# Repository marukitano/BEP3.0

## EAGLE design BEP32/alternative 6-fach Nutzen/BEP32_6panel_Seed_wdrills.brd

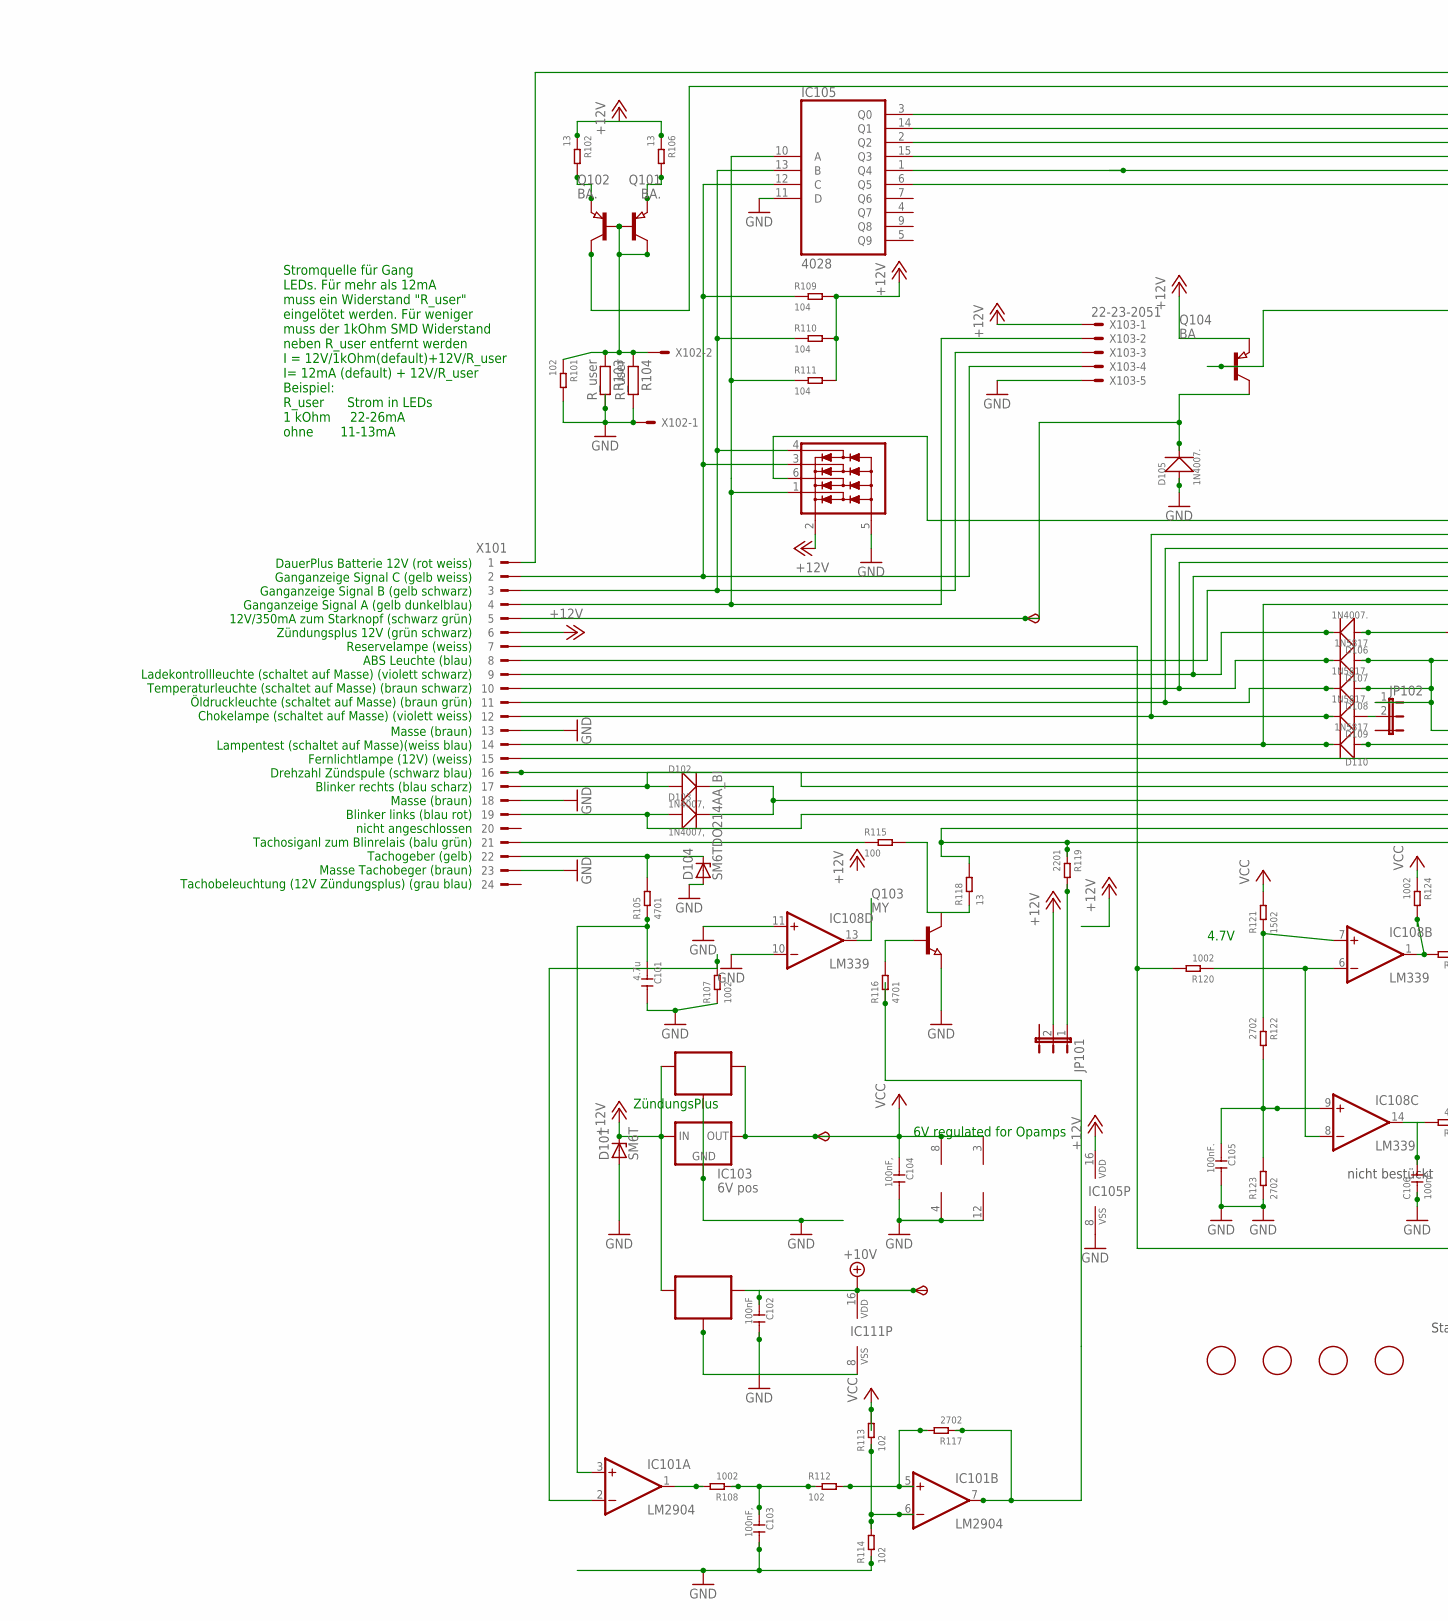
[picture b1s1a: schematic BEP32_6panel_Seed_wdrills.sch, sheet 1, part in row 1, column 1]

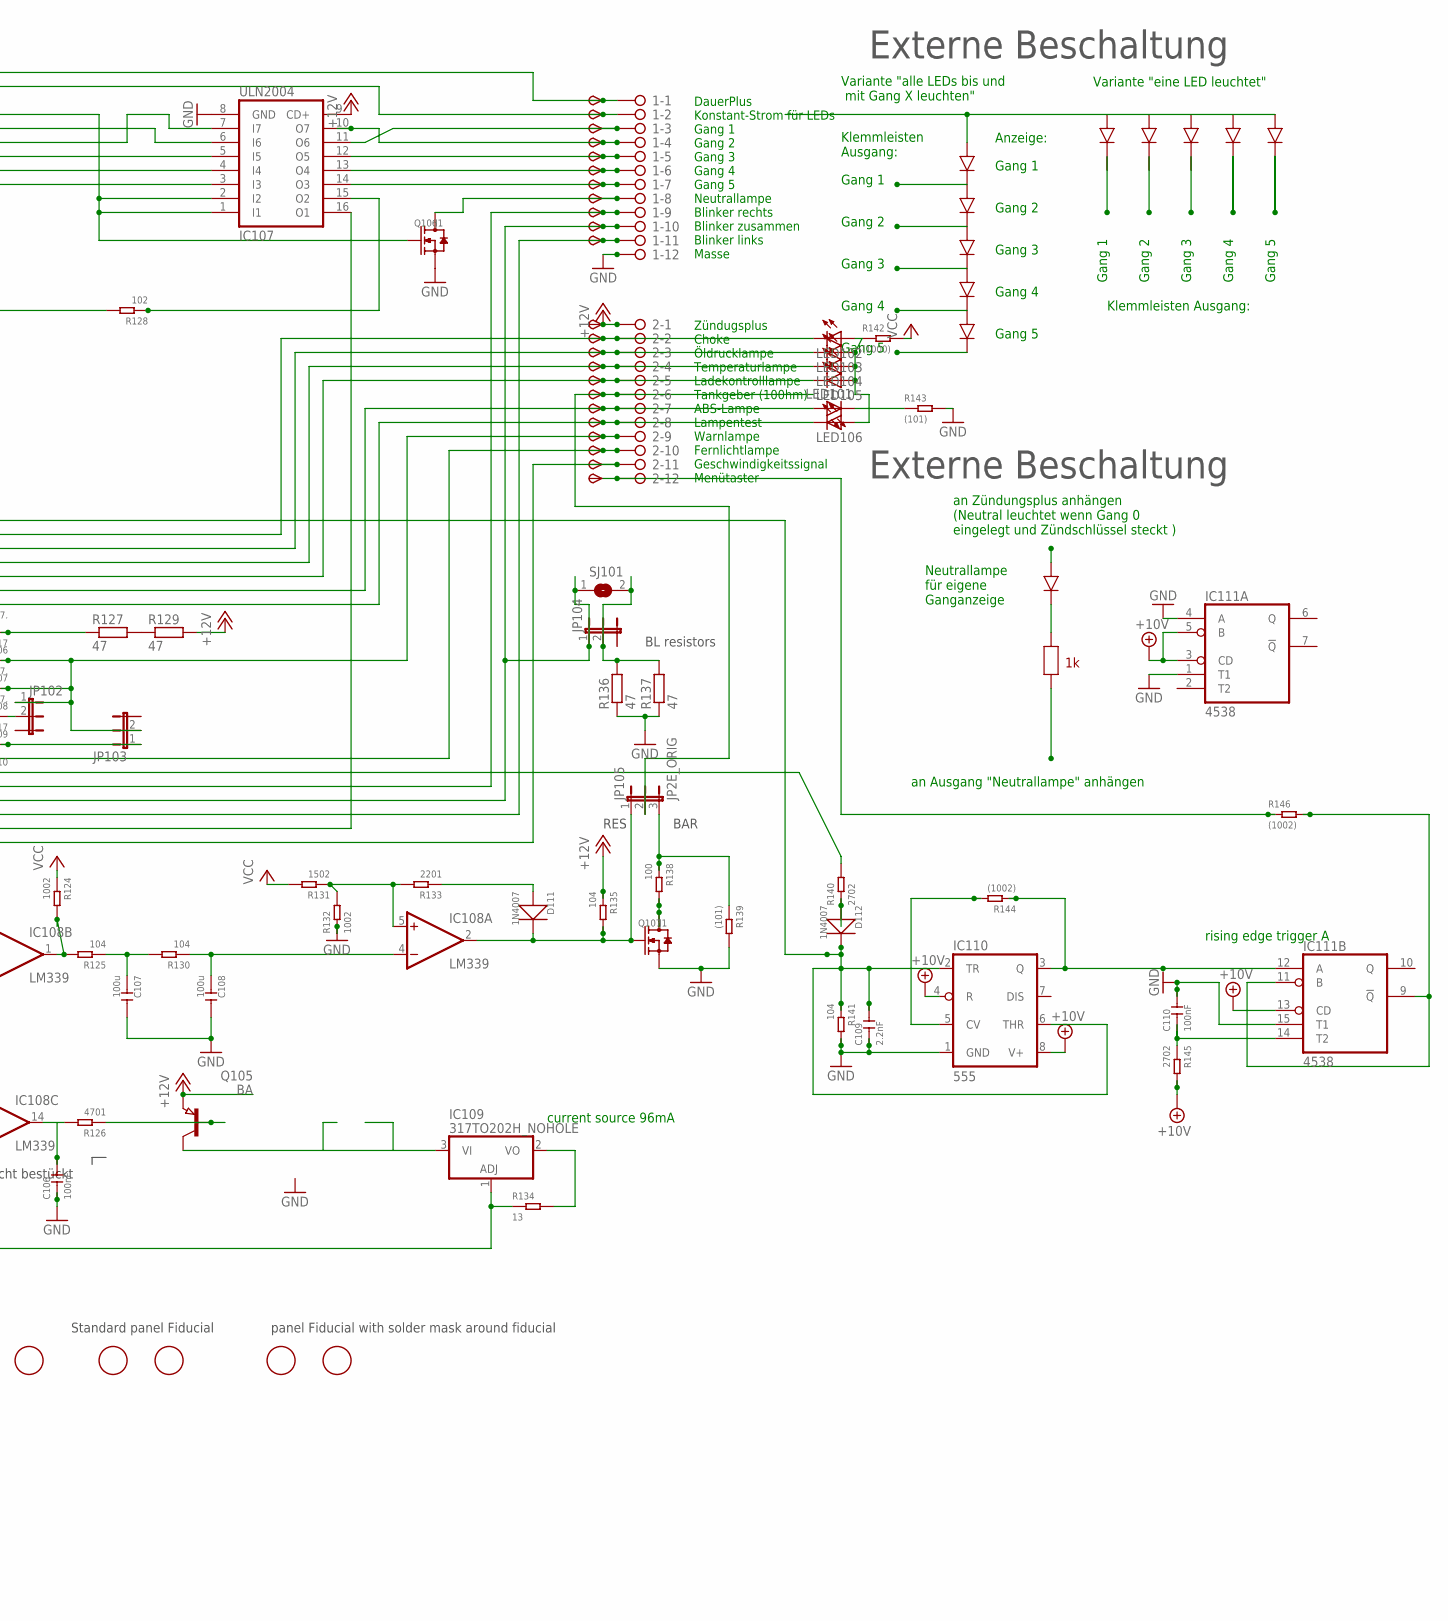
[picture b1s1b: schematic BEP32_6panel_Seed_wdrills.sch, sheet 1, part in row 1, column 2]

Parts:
1, 2: 2081-1132; 12-PIN
6V, 10V: TPSB2.0; B2.0
C101: 4.7u; C0805
C102, C110: 100nF; C0805
C103, C104: 100nF,; C0805
C105, C106: 100nF.; C0805
C107, C108: 100u; C1206
C109: 2.2nF; C0805
D101: SM6T; DO214AA
D102, D103: 1N4007,; DO-214AC
D104: SM6TDO214AA_BI; DO214AA_BI
D105, D106: 1N4007.; DO-214AC
D107, D110: 1N5817; DO-214AC_SLIM
D108, D109: 1N5817.; DO-214AC_SLIM
D111, D112: 1N4007; DO-214AC
FID1, FID2, FID101, FID102, FID103, FID104: FIDUCIAL; FIDUCIAL_1MM
FID1B, FID2B: FIDUCIALFIDUCIAL_1MM_WITH_SOLDERMASK; FIDUCIAL_1MM_WITH_SOLDERMASK
IC101: LM2904; SO08
IC102: 78L06; SOT89_ROUND
IC103: 6V pos; 78LXX
IC104: 78L10; SOT89_ROUND
IC105: 4028; SO16
IC106: NUP4304SOT457_R; SOT457R_PHILIPS
IC107: ULN2004; SO16
IC108: LM339; SO14
IC109: 317TO202H_NOHOLE; TO220H_NOHOLE
IC110: 555; SO08
IC111: 4538; SO16
JP101, JP102, JP103, JP104: JP2EJP2_SMALLPADS; JP2_SMALLPADS
JP105: JP2E_ORIG; JP2_ORIG_SMALLPADS
LED101, LED102, LED103, LED104, LED105, LED106: LEDLD260; LD260
Q101, Q102: BA.; SOT89
Q103: MY; SOT89
Q104, Q105: BA; SOT89
Q106, Q107: J1; SOT-23
R101, R112, R113, R114, R128: 102; R0805
R102, R106, R118, R134: 13; R1206
R103, R104: R_user; R0805
R105, R116, R126: 4701; R0805
R107, R108, R120, R124, R132: 1002; R0805
R109, R110, R111, R125, R130, R135, R141: 104; R0805
R115, R138: 100; R0805
R117, R122, R123, R140, R145: 2702; R0805
R119, R133: 2201; R0805
R121, R131: 1502; R0805
R127, R129, R136, R137: 47; V235/17_1MM
R139, R143: (101); R0805
R142: (1000); R0805
R144, R146: (1002); R0805
SJ101: SJ
START: TPSB2.0; B2.0
TP1, TP2, TP3, TP4, TP5, TP6, TP7, TP8, TP9, TP10, TP11, TP12, TP13, TP16, TP17, TP18, TP19, TP21, TP22, TP23, TP25, TP26: TPSB2.0; B2.0
TP24: TPSB1,27; B1,27
X101: CON_BMWV2; 24-PIN_V2
X102: 22-23-2021
X103: 22-23-2051

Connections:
+10V: 10V.TP, C102.1, IC104.1 (OUT), IC110.4 (R), IC110.8 (V+), IC111.3 (CD), IC111.5 (B), IC111.13 (CD), IC111.16 (VDD), R145.2; also elsewhere on the board
+12V: 2.1, D101.C, IC102.3 (IN), IC103.IN, IC104.3 (IN), IC105.16 (VDD), IC106.2 (V+), IC107.9 (CD+), JP101.2, Q104.3 (E), Q105.3 (E), R102.1, R106.1, R109.2, R110.2, R111.2, R129.2, R135.1, TP12.TP, X101.6, X103.1; also elsewhere on the board
+12V1: IC101.7 (OUT), R116.1, R117.1
GND: 1.12, C101.2, C102.2, C103.2, C104.2, C105.2, C106.1, C107.2, C108.2, C109.1, C110.2, D101.A, D104.A, D105.1 (+), IC101.4 (V-), IC102.2 (GND), IC102.2@1 (GND), IC103.GND, IC104.2 (GND), IC104.2@1 (GND), IC105.8 (VSS), IC105.11 (D), IC106.5 (V-), IC107.8 (GND), IC108.10 (-IN), IC108.11 (+IN), IC108.12 (GND), IC110.1 (GND), IC111.1 (T1), IC111.4 (A), IC111.8 (VSS), IC111.15 (T1), Q103.3 (E), Q106.2 (S), Q107.2 (S), R101.2, R103.2, R104.2, R107.1, R114.1, R123.1, R132.1, R136.1, R137.1, R139.2, R141.2, R143.2, X101.13, X101.18, X101.23, X102.1, X103.5; also elsewhere on the board
unnamed: 2.9, D107.1 (+), D108.1 (+), JP102.1, JP103.2, TP24.TP
unnamed: IC105.10 (A), IC106.1 (D1), R111.1, X101.4, X103.2
unnamed: IC105.13 (B), IC106.4 (D4), R110.1, X101.3, X103.3
unnamed: 2.7, LED101.A, TP22.TP, X101.8
unnamed: Q101.3 (E), R102.2
unnamed: D111.2 (-), IC108.2 (OUT), JP105.1, Q107.1 (G), R135.2
unnamed: IC101.2 (-IN), R107.2
unnamed: R127.2, R129.1
unnamed: Q102.3 (E), R106.2
unnamed: D105.2 (-), Q104.2 (C), START.TP, X101.5
unnamed: 2.2, D109.2 (-), LED102.K (C), TP16.TP, X101.12
unnamed: 2.3, D108.2 (-), LED103.K (C), TP17.TP, X101.11
unnamed: 2.4, D107.2 (-), LED104.K (C), TP18.TP, X101.10
unnamed: IC109.3 (VI), Q105.2 (C)
unnamed: IC108.6 (-IN), IC108.8 (-IN), R120.1
unnamed: IC105.12 (C), IC106.3 (D3), R109.1, X101.2, X103.4
unnamed: IC105.15 (Q3), IC107.5 (I5)
unnamed: 2.8, D110.2 (-), LED106.K (C), TP23.TP, X101.14
unnamed: 1.9, D102.1 (+), TP9.TP, X101.17
unnamed: 1.11, D103.1 (+), TP11.TP, X101.19
unnamed: IC111.9 (!Q), IC111.11 (B), R146.2
unnamed: D104.C, R105.2, X101.22
unnamed: C101.1, IC101.3 (+IN), R105.1
unnamed: 1.6, IC107.13 (O4), TP6.TP
unnamed: 1.7, IC107.14 (O3), TP7.TP
unnamed: 2.11, IC107.16 (O1), R118.2, R119.1, TP26.TP
unnamed: 2.6, JP105.2, TP21.TP
unnamed: JP101.1, R119.2
unnamed: C105.1, IC108.9 (+IN), R122.2, R123.2
unnamed: C106.2, IC108.14 (OUT), R126.2
unnamed: C109.2, D112.2 (-), IC106.6 (D2), IC110.2 (TR), IC110.6 (THR), R141.1
unnamed: LED101.K (C), R143.1
unnamed: IC109.1 (ADJ), R120.2, R134.1, X101.7
unnamed: Q105.1 (B), R126.1
unnamed: IC105.2 (Q2), IC107.7 (I7)
unnamed: 1.3, IC107.11 (O6), TP3.TP
unnamed: 1.5, IC107.12 (O5), TP5.TP
unnamed: LED102.A, LED103.A, LED104.A, LED105.A, LED106.A, R142.1
unnamed: R140.2, X101.16
unnamed: Q104.1 (B), R128.2
unnamed: IC105.3 (Q0), IC107.1 (I1), IC107.2 (I2), Q106.1 (G)
unnamed: C107.1, R125.1, R130.2
unnamed: C108.1, IC108.4 (-IN), R130.1
unnamed: IC108.5 (+IN), R131.1, R132.2, R133.2
unnamed: Q107.3 (D), R138.2
unnamed: D111.1 (+), R133.1
unnamed: IC105.1 (Q4), IC107.4 (I4)
unnamed: R115.1, X101.21
unnamed: 1.8, Q106.3 (D), TP8.TP
unnamed: 2.10, TP25.TP, X101.15
unnamed: D106.1 (+), R127.1
unnamed: 2.5, D106.2 (-), LED105.K (C), TP19.TP, X101.9
unnamed: IC105.14 (Q1), IC107.6 (I6)
unnamed: Q101.1 (B), Q102.1 (B), Q102.2 (C), R101.1, R103.1, R104.1, X102.2
unnamed: Q103.2 (C), R115.2, R118.1
unnamed: 1.2, Q101.2 (C), TP2.TP
unnamed: IC105.6 (Q5), IC107.3 (I3)
unnamed: IC109.2 (VO), R134.2
unnamed: IC110.5 (CV), R144.2
unnamed: 1.4, IC107.10 (O7), TP4.TP
unnamed: 1.1, TP1.TP, X101.1
unnamed: IC108.7 (+IN), R121.1, R122.1
unnamed: Q103.1 (B), R116.2
unnamed: IC110.3 (Q), IC111.12 (A), R144.1
unnamed: D112.1 (+), R140.1
unnamed: IC107.15 (O2), R128.1
unnamed: C110.1, IC111.14 (T2), R145.1
unnamed: 2.12, R146.1, TP13.TP
unnamed: IC101.1 (OUT), R108.2
unnamed: 1.10, D102.2 (-), D103.2 (-), JP104.1, SJ101.1, TP10.TP
unnamed: JP104.2, R136.2, R137.2, SJ101.2
unnamed: D109.1 (+), JP102.2
unnamed: C103.1, R108.1, R112.1
unnamed: IC101.5 (+IN), R112.2, R117.2
unnamed: D110.1 (+), JP103.1
unnamed: JP105.3, R138.1, R139.1
unnamed: IC101.6 (-IN), R113.1, R114.2
unnamed: IC108.1 (OUT), R124.2, R125.2
VCC: 6V.TP, C104.1, IC101.8 (V+), IC102.1 (OUT), IC103.OUT, IC108.3 (V+), R113.2, R121.2, R124.1, R131.2, R142.2; also elsewhere on the board

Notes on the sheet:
6V regulated for Opamps
current source 96mA
ZündungsPlus
Zündugsplus Choke Öldrucklampe Temperaturlampe Ladekontrolllampe Tankgeber (100hm) ABS-Lampe Lampentest Warnlampe Fernlichtlampe Geschwindigkeitssignal Menütaster
DauerPlus Konstant-Strom für LEDs Gang 1 Gang 2 Gang 3 Gang 4 Gang 5 Neutrallampe Blinker rechts Blinker zusammen Blinker links Masse
DauerPlus Batterie 12V (rot weiss) Ganganzeige Signal C (gelb weiss) Ganganzeige Signal B (gelb schwarz) Ganganzeige Signal A (gelb dunkelblau) 12V/350mA zum Starknopf (schwarz grün) Zündungsplus 12V (grün schwarz) Reservelampe (weiss) ABS Leuchte (blau) Ladekontrollleuchte (schaltet auf Masse) (vi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
Masse (braun) Lampentest (schaltet auf Masse)(weiss blau) Fernlichtlampe (12V) (weiss) Drehzahl Zündspule (schwarz blau) Blinker rechts (blau scharz) Masse (braun) Blinker links (blau rot) nicht angeschlossen Tachosiganl zum Blinrelais (balu grün) Tachogeber (gelb) Masse Tachobeger (braun) Tachobel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
4.7V
Stromquelle für Gang LEDs. Für mehr als 12mA muss ein Widerstand "R_user" eingelötet werden. Für weniger muss der 1kOhm SMD Widerstand neben R_user entfernt werden I = 12V/1kOhm(default)+12V/R_user I= 12mA (default) + 12V/R_user Beispiel: R_user Strom in LEDs 1 kOhm 22-26mA ohne 11-13mA
Gang 1
Gang 2
Gang 3
Gang 4
Gang 5
Variante "eine LED leuchtet"
Variante "alle LEDs bis und mit Gang X leuchten"
Klemmleisten Ausgang:
Klemmleisten Ausgang:
an Zündungsplus anhängen (Neutral leuchtet wenn Gang 0 eingelegt und Zündschlüssel steckt )
an Ausgang "Neutrallampe" anhängen
Neutrallampe für eigene Ganganzeige
Externe Beschaltung
Anzeige:
nicht bestückt
rising edge trigger A
BAR
RES
BL resistors
Standard panel Fiducial
panel Fiducial with solder mask around fiducial

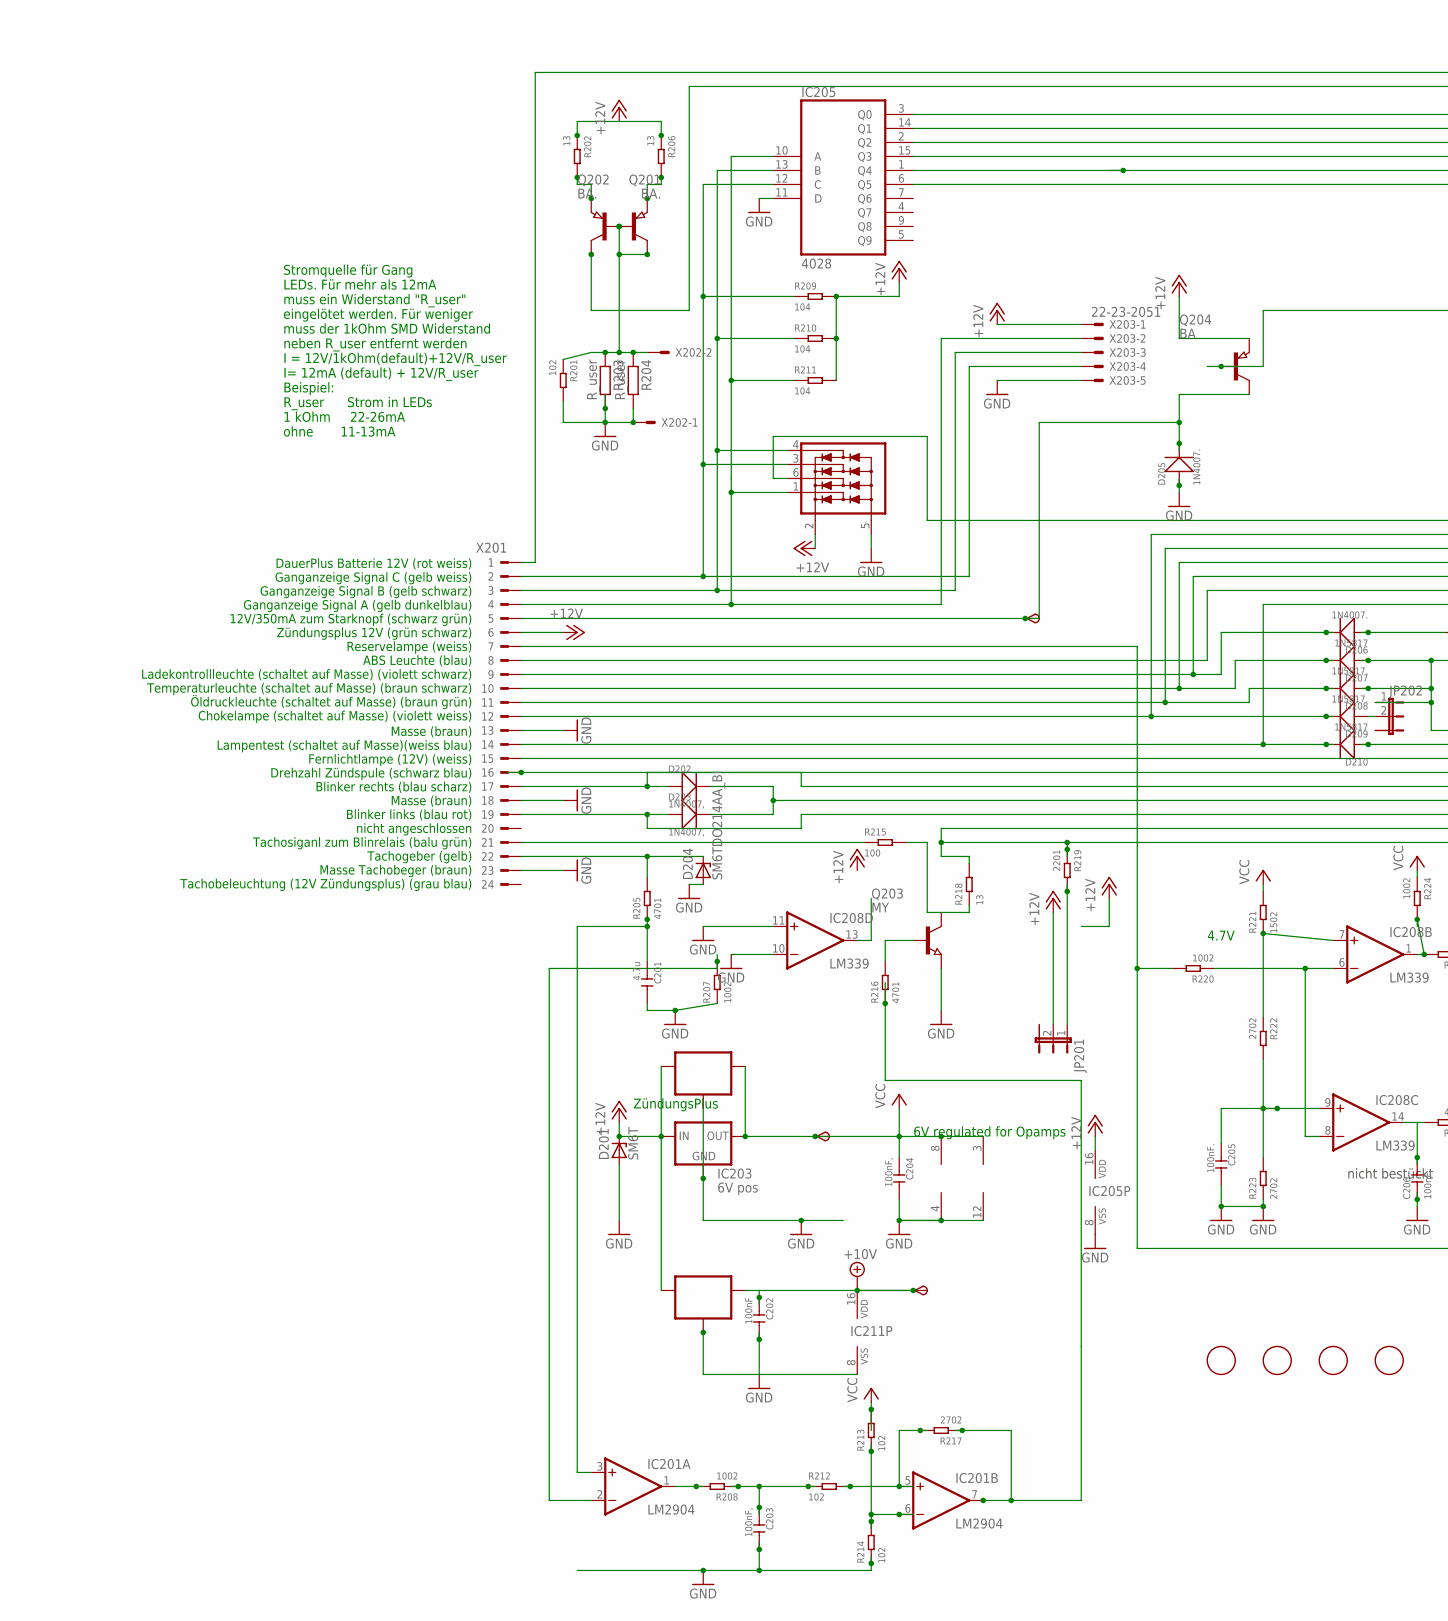
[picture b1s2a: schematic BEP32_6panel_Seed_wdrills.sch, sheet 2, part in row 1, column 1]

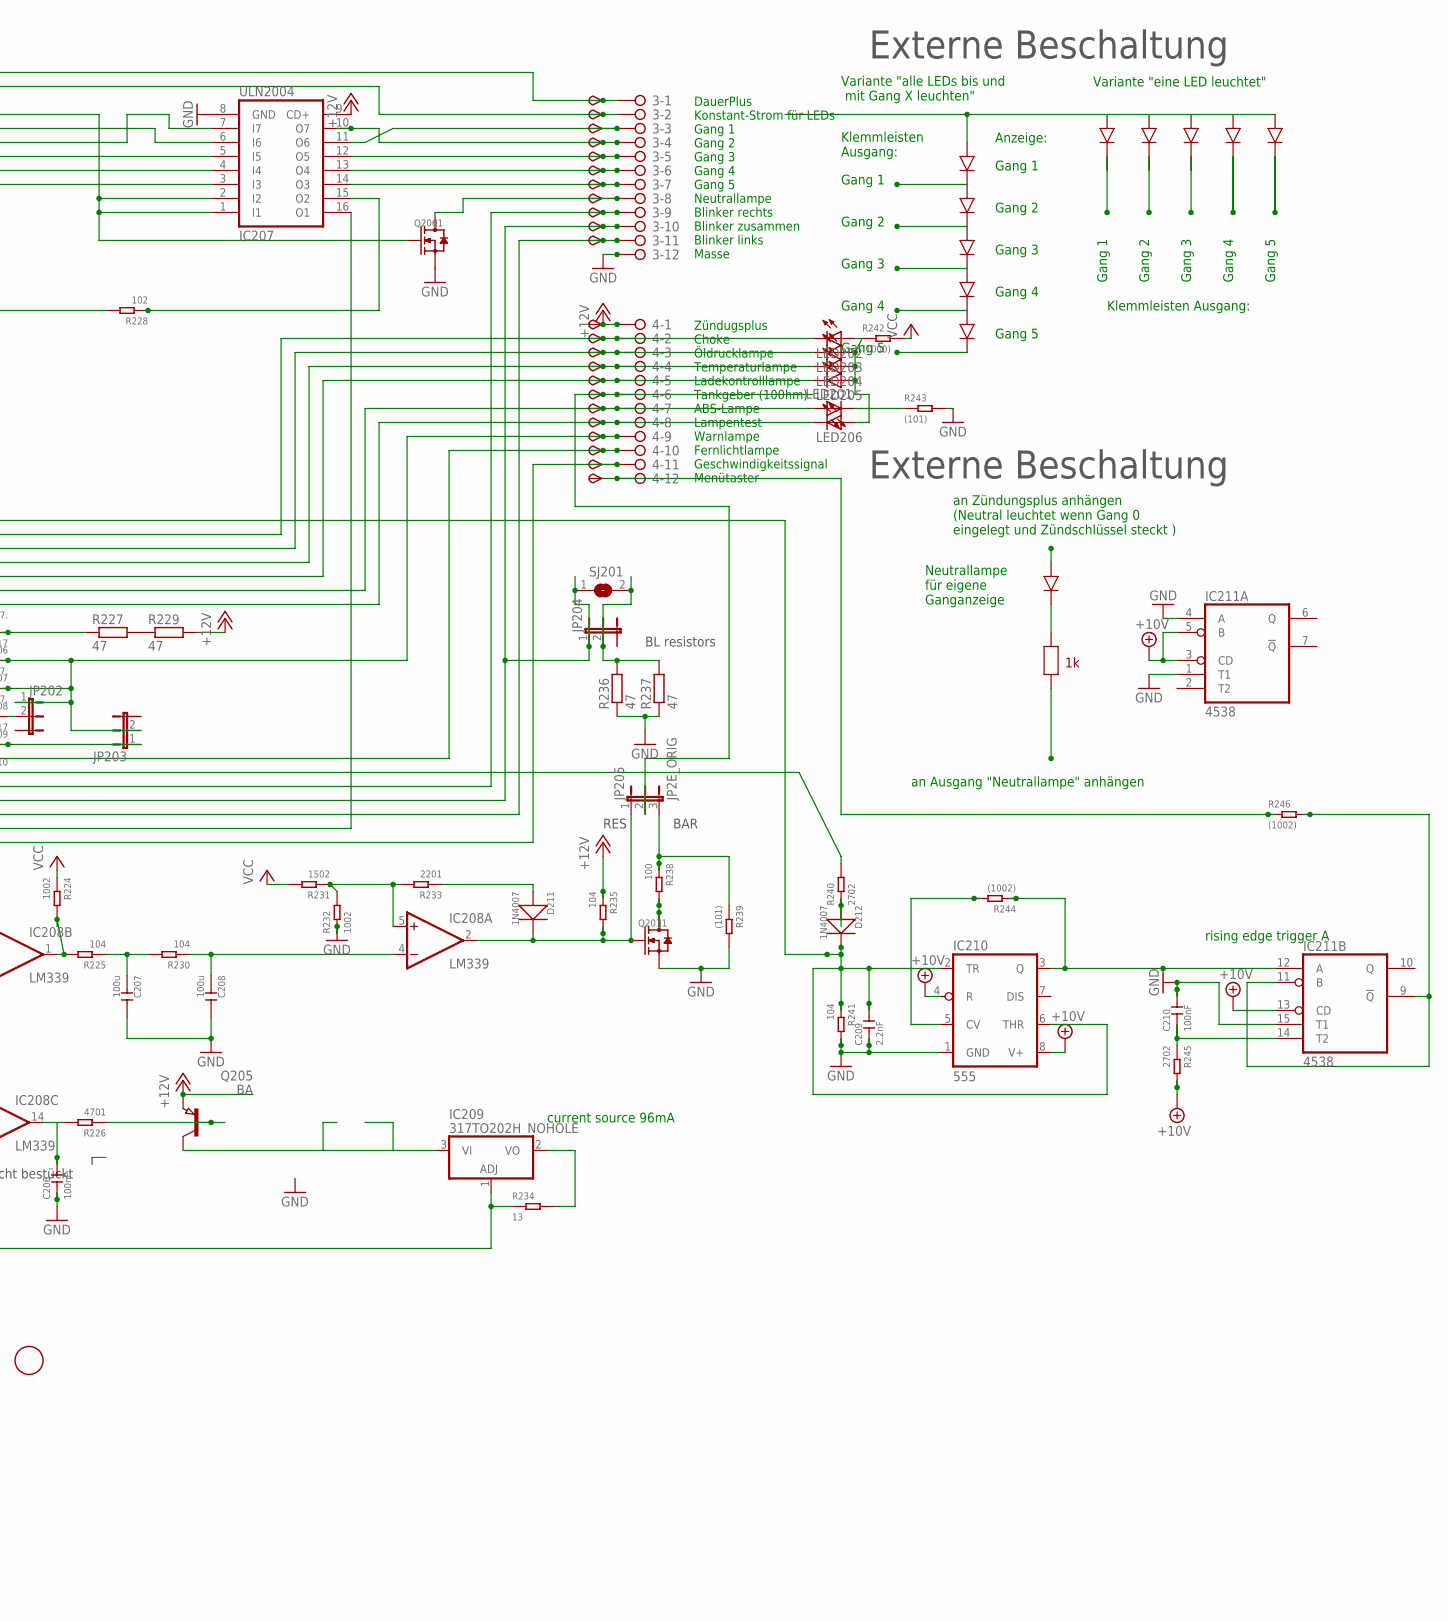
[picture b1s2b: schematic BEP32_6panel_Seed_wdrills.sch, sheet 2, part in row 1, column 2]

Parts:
3, 4: 2081-1132; 12-PIN
6V201, 10V201: TPSB2.0; B2.0
C201: 4.7u; C0805
C202, C210: 100nF; C0805
C203, C204: 100nF,; C0805
C205, C206: 100nF.; C0805
C207, C208: 100u; C1206
C209: 2.2nF; C0805
D201: SM6T; DO214AA
D202, D203: 1N4007,; DO-214AC
D204: SM6TDO214AA_BI; DO214AA_BI
D205, D206: 1N4007.; DO-214AC
D207, D210: 1N5817; DO-214AC_SLIM
D208, D209: 1N5817.; DO-214AC_SLIM
D211, D212: 1N4007; DO-214AC
FID201, FID202, FID203, FID204: FIDUCIAL; FIDUCIAL_1MM
IC201: LM2904; SO08
IC202: 78L06; SOT89_ROUND
IC203: 6V pos; 78LXX
IC204: 78L10; SOT89_ROUND
IC205: 4028; SO16
IC206: NUP4304SOT457_R; SOT457R_PHILIPS
IC207: ULN2004; SO16
IC208: LM339; SO14
IC209: 317TO202H_NOHOLE; TO220H_NOHOLE
IC210: 555; SO08
IC211: 4538; SO16
JP201, JP202, JP203, JP204: JP2EJP2_SMALLPADS; JP2_SMALLPADS
JP205: JP2E_ORIG; JP2_ORIG_SMALLPADS
LED201, LED202, LED203, LED204, LED205, LED206: LEDLD260; LD260
Q201, Q202: BA.; SOT89
Q203: MY; SOT89
Q204, Q205: BA; SOT89
Q206, Q207: J1; SOT-23
R201, R212, R213, R214, R228: 102; R0805
R202, R206, R218, R234: 13; R1206
R203, R204: R_user; R0805
R205, R216, R226: 4701; R0805
R207, R208, R220, R224, R232: 1002; R0805
R209, R210, R211, R225, R230, R235, R241: 104; R0805
R215, R238: 100; R0805
R217, R222, R223, R240, R245: 2702; R0805
R219, R233: 2201; R0805
R221, R231: 1502; R0805
R227, R229, R236, R237: 47; V235/17_1MM
R239, R243: (101); R0805
R242: (1000); R0805
R244, R246: (1002); R0805
SJ201: SJ
START201: TPSB2.0; B2.0
TP14, TP15, TP20, TP27, TP28, TP29, TP30, TP31, TP32, TP33, TP34, TP35, TP36, TP37, TP38, TP39, TP40, TP41, TP43, TP44, TP45, TP46: TPSB2.0; B2.0
TP42: TPSB1,27; B1,27
X201: CON_BMWV2; 24-PIN_V2
X202: 22-23-2021
X203: 22-23-2051

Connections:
+10V: 10V201.TP, C202.1, IC204.1 (OUT), IC210.4 (R), IC210.8 (V+), IC211.3 (CD), IC211.5 (B), IC211.13 (CD), IC211.16 (VDD), R245.2; also elsewhere on the board
+12V: 4.1, D201.C, IC202.3 (IN), IC203.IN, IC204.3 (IN), IC205.16 (VDD), IC206.2 (V+), IC207.9 (CD+), JP201.2, Q204.3 (E), Q205.3 (E), R202.1, R206.1, R209.2, R210.2, R211.2, R229.2, R235.1, TP45.TP, X201.6, X203.1; also elsewhere on the board
+12V2: IC201.7 (OUT), R216.1, R217.1
GND: 3.12, C201.2, C202.2, C203.2, C204.2, C205.2, C206.1, C207.2, C208.2, C209.1, C210.2, D201.A, D204.A, D205.1 (+), IC201.4 (V-), IC202.2 (GND), IC202.2@1 (GND), IC203.GND, IC204.2 (GND), IC204.2@1 (GND), IC205.8 (VSS), IC205.11 (D), IC206.5 (V-), IC207.8 (GND), IC208.10 (-IN), IC208.11 (+IN), IC208.12 (GND), IC210.1 (GND), IC211.1 (T1), IC211.4 (A), IC211.8 (VSS), IC211.15 (T1), Q203.3 (E), Q206.2 (S), Q207.2 (S), R201.2, R203.2, R204.2, R207.1, R214.1, R223.1, R232.1, R236.1, R237.1, R239.2, R241.2, R243.2, X201.13, X201.18, X201.23, X202.1, X203.5; also elsewhere on the board
unnamed: R227.2, R229.1
unnamed: 4.9, D207.1 (+), D208.1 (+), JP202.1, JP203.2, TP42.TP
unnamed: IC205.10 (A), IC206.1 (D1), R211.1, X201.4, X203.2
unnamed: IC205.13 (B), IC206.4 (D4), R210.1, X201.3, X203.3
unnamed: D205.2 (-), Q204.2 (C), START201.TP, X201.5
unnamed: IC205.12 (C), IC206.3 (D3), R209.1, X201.2, X203.4
unnamed: 4.7, LED201.A, TP40.TP, X201.8
unnamed: 4.2, D209.2 (-), LED202.K (C), TP35.TP, X201.12
unnamed: 4.3, D208.2 (-), LED203.K (C), TP36.TP, X201.11
unnamed: 4.4, D207.2 (-), LED204.K (C), TP37.TP, X201.10
unnamed: 4.8, D210.2 (-), LED206.K (C), TP41.TP, X201.14
unnamed: 3.9, D202.1 (+), TP32.TP, X201.17
unnamed: 3.11, D203.1 (+), TP34.TP, X201.19
unnamed: D204.C, R205.2, X201.22
unnamed: C201.1, IC201.3 (+IN), R205.1
unnamed: 4.11, IC207.16 (O1), R218.2, R219.1, TP44.TP
unnamed: IC208.1 (OUT), R224.2, R225.2
unnamed: C207.1, R225.1, R230.2
unnamed: C208.1, IC208.4 (-IN), R230.1
unnamed: IC208.5 (+IN), R231.1, R232.2, R233.2
unnamed: D211.1 (+), R233.1
unnamed: C205.1, IC208.9 (+IN), R222.2, R223.2
unnamed: C206.2, IC208.14 (OUT), R226.2
unnamed: Q205.1 (B), R226.1
unnamed: IC205.2 (Q2), IC207.7 (I7)
unnamed: 3.5, IC207.12 (O5), TP28.TP
unnamed: IC205.1 (Q4), IC207.4 (I4)
unnamed: 3.8, Q206.3 (D), TP31.TP
unnamed: 4.10, TP43.TP, X201.15
unnamed: 4.5, D206.2 (-), LED205.K (C), TP38.TP, X201.9
unnamed: D206.1 (+), R227.1
unnamed: IC205.6 (Q5), IC207.3 (I3)
unnamed: 3.4, IC207.10 (O7), TP27.TP
unnamed: IC209.1 (ADJ), R220.2, R234.1, X201.7
unnamed: IC208.6 (-IN), IC208.8 (-IN), R220.1
unnamed: 3.2, Q201.2 (C), TP15.TP
unnamed: 3.1, TP14.TP, X201.1
unnamed: R240.2, X201.16
unnamed: IC205.15 (Q3), IC207.5 (I5)
unnamed: 3.6, IC207.13 (O4), TP29.TP
unnamed: 3.7, IC207.14 (O3), TP30.TP
unnamed: 4.6, JP205.2, TP39.TP
unnamed: LED201.K (C), R243.1
unnamed: LED202.A, LED203.A, LED204.A, LED205.A, LED206.A, R242.1
unnamed: Q204.1 (B), R228.2
unnamed: IC205.3 (Q0), IC207.1 (I1), IC207.2 (I2), Q206.1 (G)
unnamed: IC205.14 (Q1), IC207.6 (I6)
unnamed: 3.3, IC207.11 (O6), TP20.TP
unnamed: Q201.1 (B), Q202.1 (B), Q202.2 (C), R201.1, R203.1, R204.1, X202.2
unnamed: Q201.3 (E), R202.2
unnamed: Q202.3 (E), R206.2
unnamed: IC208.7 (+IN), R221.1, R222.1
unnamed: IC201.2 (-IN), R207.2
unnamed: Q203.1 (B), R216.2
unnamed: Q207.3 (D), R238.2
unnamed: IC209.2 (VO), R234.2
unnamed: IC209.3 (VI), Q205.2 (C)
unnamed: C209.2, D212.2 (-), IC206.6 (D2), IC210.2 (TR), IC210.6 (THR), R241.1
unnamed: IC210.5 (CV), R244.2
unnamed: IC210.3 (Q), IC211.12 (A), R244.1
unnamed: D212.1 (+), R240.1
unnamed: 3.10, D202.2 (-), D203.2 (-), JP204.1, SJ201.1, TP33.TP
unnamed: JP204.2, R236.2, R237.2, SJ201.2
unnamed: IC211.9 (!Q), IC211.11 (B), R246.2
unnamed: C210.1, IC211.14 (T2), R245.1
unnamed: JP201.1, R219.2
unnamed: IC207.15 (O2), R228.1
unnamed: 4.12, R246.1, TP46.TP
unnamed: D209.1 (+), JP202.2
unnamed: D211.2 (-), IC208.2 (OUT), JP205.1, Q207.1 (G), R235.2
unnamed: IC201.1 (OUT), R208.2
unnamed: C203.1, R208.1, R212.1
unnamed: IC201.5 (+IN), R212.2, R217.2
unnamed: IC201.6 (-IN), R213.1, R214.2
unnamed: D210.1 (+), JP203.1
unnamed: JP205.3, R238.1, R239.1
unnamed: R215.1, X201.21
unnamed: Q203.2 (C), R215.2, R218.1
VCC: 6V201.TP, C204.1, IC201.8 (V+), IC202.1 (OUT), IC203.OUT, IC208.3 (V+), R213.2, R221.2, R224.1, R231.2, R242.2; also elsewhere on the board

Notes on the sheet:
6V regulated for Opamps
current source 96mA
ZündungsPlus
Zündugsplus Choke Öldrucklampe Temperaturlampe Ladekontrolllampe Tankgeber (100hm) ABS-Lampe Lampentest Warnlampe Fernlichtlampe Geschwindigkeitssignal Menütaster
DauerPlus Konstant-Strom für LEDs Gang 1 Gang 2 Gang 3 Gang 4 Gang 5 Neutrallampe Blinker rechts Blinker zusammen Blinker links Masse
DauerPlus Batterie 12V (rot weiss) Ganganzeige Signal C (gelb weiss) Ganganzeige Signal B (gelb schwarz) Ganganzeige Signal A (gelb dunkelblau) 12V/350mA zum Starknopf (schwarz grün) Zündungsplus 12V (grün schwarz) Reservelampe (weiss) ABS Leuchte (blau) Ladekontrollleuchte (schaltet auf Masse) (vi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
Masse (braun) Lampentest (schaltet auf Masse)(weiss blau) Fernlichtlampe (12V) (weiss) Drehzahl Zündspule (schwarz blau) Blinker rechts (blau scharz) Masse (braun) Blinker links (blau rot) nicht angeschlossen Tachosiganl zum Blinrelais (balu grün) Tachogeber (gelb) Masse Tachobeger (braun) Tachobel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
4.7V
Stromquelle für Gang LEDs. Für mehr als 12mA muss ein Widerstand "R_user" eingelötet werden. Für weniger muss der 1kOhm SMD Widerstand neben R_user entfernt werden I = 12V/1kOhm(default)+12V/R_user I= 12mA (default) + 12V/R_user Beispiel: R_user Strom in LEDs 1 kOhm 22-26mA ohne 11-13mA
Gang 1
Gang 2
Gang 3
Gang 4
Gang 5
Variante "eine LED leuchtet"
Variante "alle LEDs bis und mit Gang X leuchten"
Klemmleisten Ausgang:
Klemmleisten Ausgang:
an Zündungsplus anhängen (Neutral leuchtet wenn Gang 0 eingelegt und Zündschlüssel steckt )
an Ausgang "Neutrallampe" anhängen
Neutrallampe für eigene Ganganzeige
Externe Beschaltung
Anzeige:
nicht bestückt
rising edge trigger A
BAR
RES
BL resistors
